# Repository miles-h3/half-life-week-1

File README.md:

My half-life week-1 files, guide @ https://github.com/SharKingStudios/Starbie/blob/main/Week%201%20Guide.md  
Contents:
- Starbie program file
- Electronics Schematic
- PCB board KiCad design file  

**Tabulated BOM:**
  
| Part | What it's for | Qty | Unit | Total | Vendor |
| --- | --- | --- | --- | --- | --- |
| [Starbie PCB](https://cart.jlcpcb.com/quote?rand=0.42471665169012707&_t=1791766472333&spm=Jlpcb.Instantquote.1008&up_spm=Jlpcb.Loginpage.1003) | wiring all components? | 5 | $0.80 | $4.00 | [JLCPCB](https://cart.jlcpcb.com/quote?rand=0.42471665169012707&_t=1791766472333&spm=Jlpcb.Instantquote.1008&up_spm=Jlpcb.Loginpage.1003) |
| [XIAO ESP32C3](https://example.com) | microcontroller | 1 | $0.55 | $0.55 | [Seeedstudio AI Hardware](https://example.com) |
| [MPU6050](https://example.com) | sensor | 1 | $2.79 | $2.79 | [Ywmsfl](https://example.com) |
| [DHT11](https://example.com) | temperature and moisture sensor | 1 | $1.99 | $1.99 | [Aihjcnele](https://example.com) |
| [0.96 OLED](https://example.com) | display | 1 | $4.99 | $4.99 | [CANADUINO](https://example.com) |
| [MX Switches](https://example.com) | interaction | 10 | $0.12 | $1.20 | [ONEFIRE Store](https://example.com) |

| Summary | Amount |
| --- | --- |
| Parts subtotal | **$15.52** |
| Tax & shipping | **$9.73** |
| Total | **$25.25** |

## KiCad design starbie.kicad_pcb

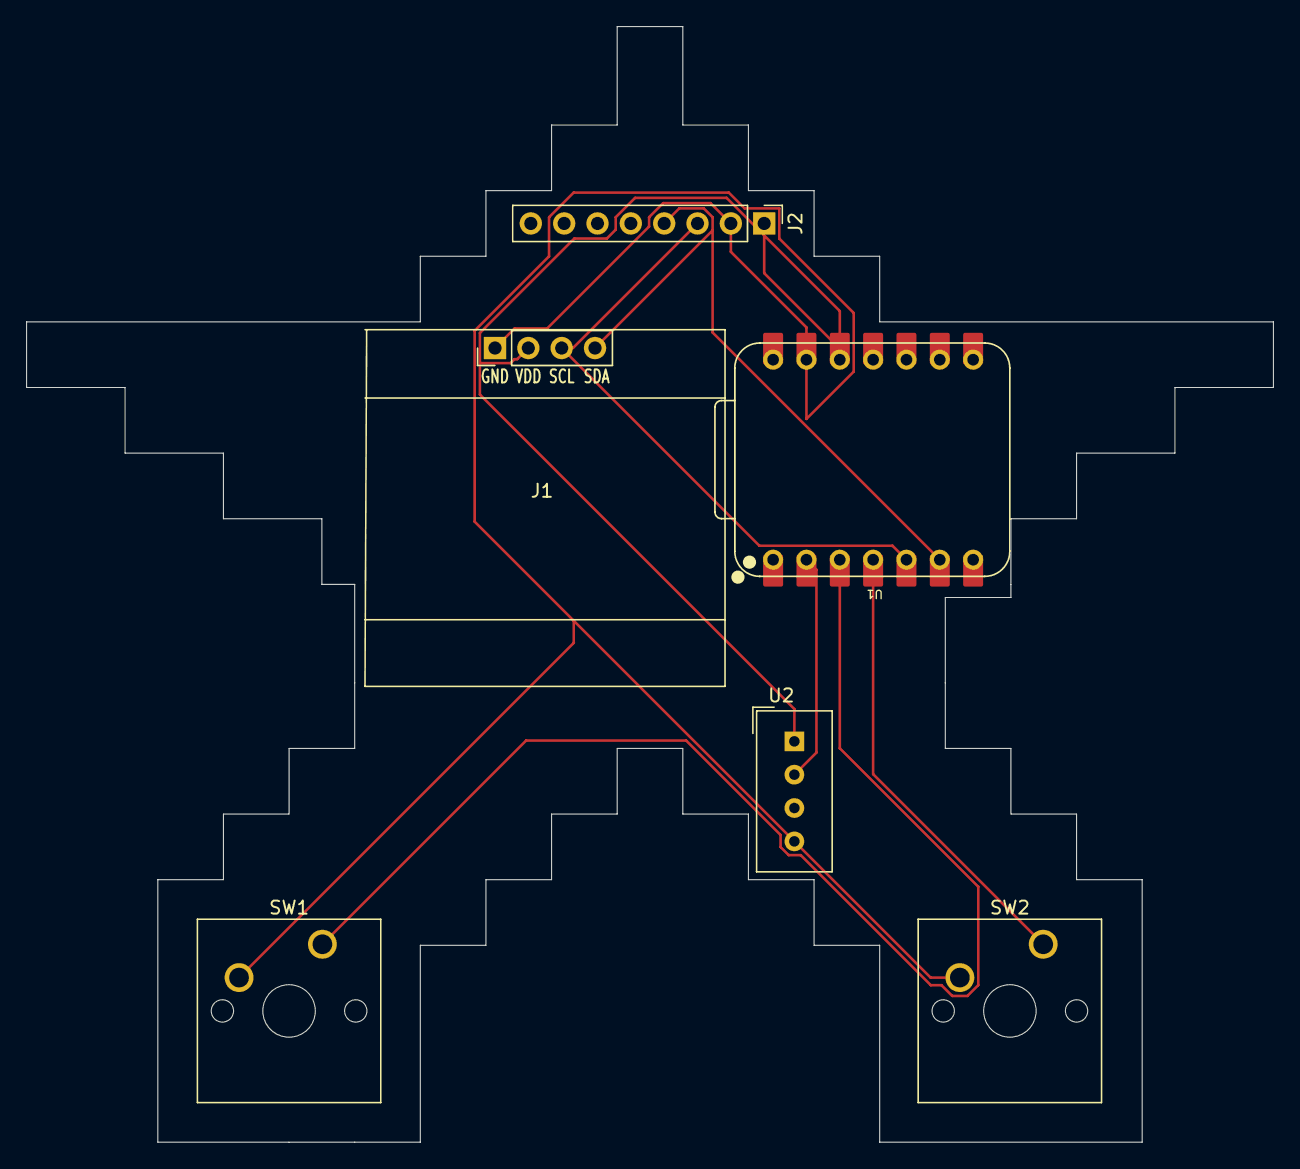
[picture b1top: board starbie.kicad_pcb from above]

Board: 2 copper layers, 95.0 x 85.0 mm, 6 parts (0 on the bottom side), 7 nets.

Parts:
J1: Conn_01x04_Pin; Display_128x64_096_I2C
J2: Conn_01x08_Pin; PinHeader_1x08_P2.54mm_Vertical
SW1, SW2: SW_Push; SW_Cherry_MX_1.00u_PCB
U1: XIAO-ESP32-C3-SMD; XIAO-ESP32-C6-DIP
U2: DHT11; Aosong_DHT11_5.5x12.0_P2.54mm

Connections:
+3.3V: J1.2, J2.1, U1.12 (3V3_OUT), U2.1 (VDD)
/DHT11 DATA: U1.2 (D1), U2.2 (DATA)
/GPI02: SW1.1, U1.3 (D2)
/GPI03: SW2.1, U1.4 (D3)
/SCL: J1.3, J2.3, U1.5 (D4)
/SDA: J1.4, J2.4, U1.6 (D5)
GND: J1.1, J2.2, SW1.2, SW2.2, U1.13 (GND), U2.4 (GND)
